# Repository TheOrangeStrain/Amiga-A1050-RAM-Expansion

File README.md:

# Amiga-A1050-RAM-Expansion
A knockoff of the A1050 front mounted RAM Expansion for the Amiga 1000

FYI: I noticed today (May 4, 2022) there is a seller on ebay [item desc: 256Kb RAM  AMIGA 1000 ( GREEN FULL SET )!!! . NEW IN STOCK] who has a number of fully assembled units for sale.  They are listed as shipping from Poland. Cost would be just over $31 USD, including shipping, to ship to the USA. 
This is NOT an endorsement of this seller.  Just passing on the information. --TOD

The problem:
I have a craiglist.com Amiga A1000 rescue. Many parts are missing. Basically I have the case, motherboard, daughterboard and power supply.  I was able to find key parts (Amiga 2000 keyboard, keyboard adapter for A1000, mouse and replacement Paula).  Howevery, the system only had 256k of RAM. This is not enough to do, well, just about anything.  Standalone RAM expansions like the A1050 are rare and often expensive if you are lucky enough to find one.  So I decided to design build my one A1050 knockoff.

Special thanks to Raffzahn on  retrocomputing.stackexchange.com. The information he supplied was critical.  Particularly since I didn't have an A1050 to probe – just online photo's and his explanation.  See this post for great info: 
https://retrocomputing.stackexchange.com/questions/5410/was-the-amiga-1000s-front-expansion-port-capable-of-anything-other-than-the-256

And the question I posted with responses from awesome and extremely helpful folks:
https://retrocomputing.stackexchange.com/questions/19893/amiga-a1050-schematic

The RAM chips are 64k x 4 bits.  Two chips are used to generate each byte.  There are low and high bytes to make up the 16 bit output.  Four pairs of chips means 64k x 4 = 256k bytes.

Drop in replacement chips (eg. From Texas Instruments) exist as well.  Other similar chips should work if the schematic is adjusted for different pinouts.  Be sure to check voltages and active levels (high / low) of course.

A fairly straight forward schematic, but I had never really thought much about RAM circuitry.  No doubt there are other ways to do this, but I wanted it to be quite similar to the original.  I used sockets for the ICs since these RAM chips have been around longer than the manufactures planned :)  Reliablity may be an issue so I wanted them to be easy to swap.  In fact, not surprisingly, 10 percent of the ones I purchased tested as bad.

There are PCB files for both unrouted and routed boards.  I find it easier to change the unrouted board then reroute nets.  I used freeRouting.jar to do the routing.

The BOM.ods file shows more detail on the parts I used.  My costs are listed and are from May and June of 2021 in U.S. Dollars.

No guarantees as I only have one A1000 to test with, but this seems to work on this system.  It would be good to hear experiences from anyone who builds one or has suggestions.

I am thinking of doing a version 2 that uses chips currently being manufactured.  If I get it working,
I will post that design and info as well.

Licencing:
CC0 1.0 Universal (CC0 1.0)
https://creativecommons.org/publicdomain/zero/1.0/

Feel free to use, modify or adapt for you own use, including commercial.

I hope this is useful for the Amiga community.
Enjoy and share.
TOD

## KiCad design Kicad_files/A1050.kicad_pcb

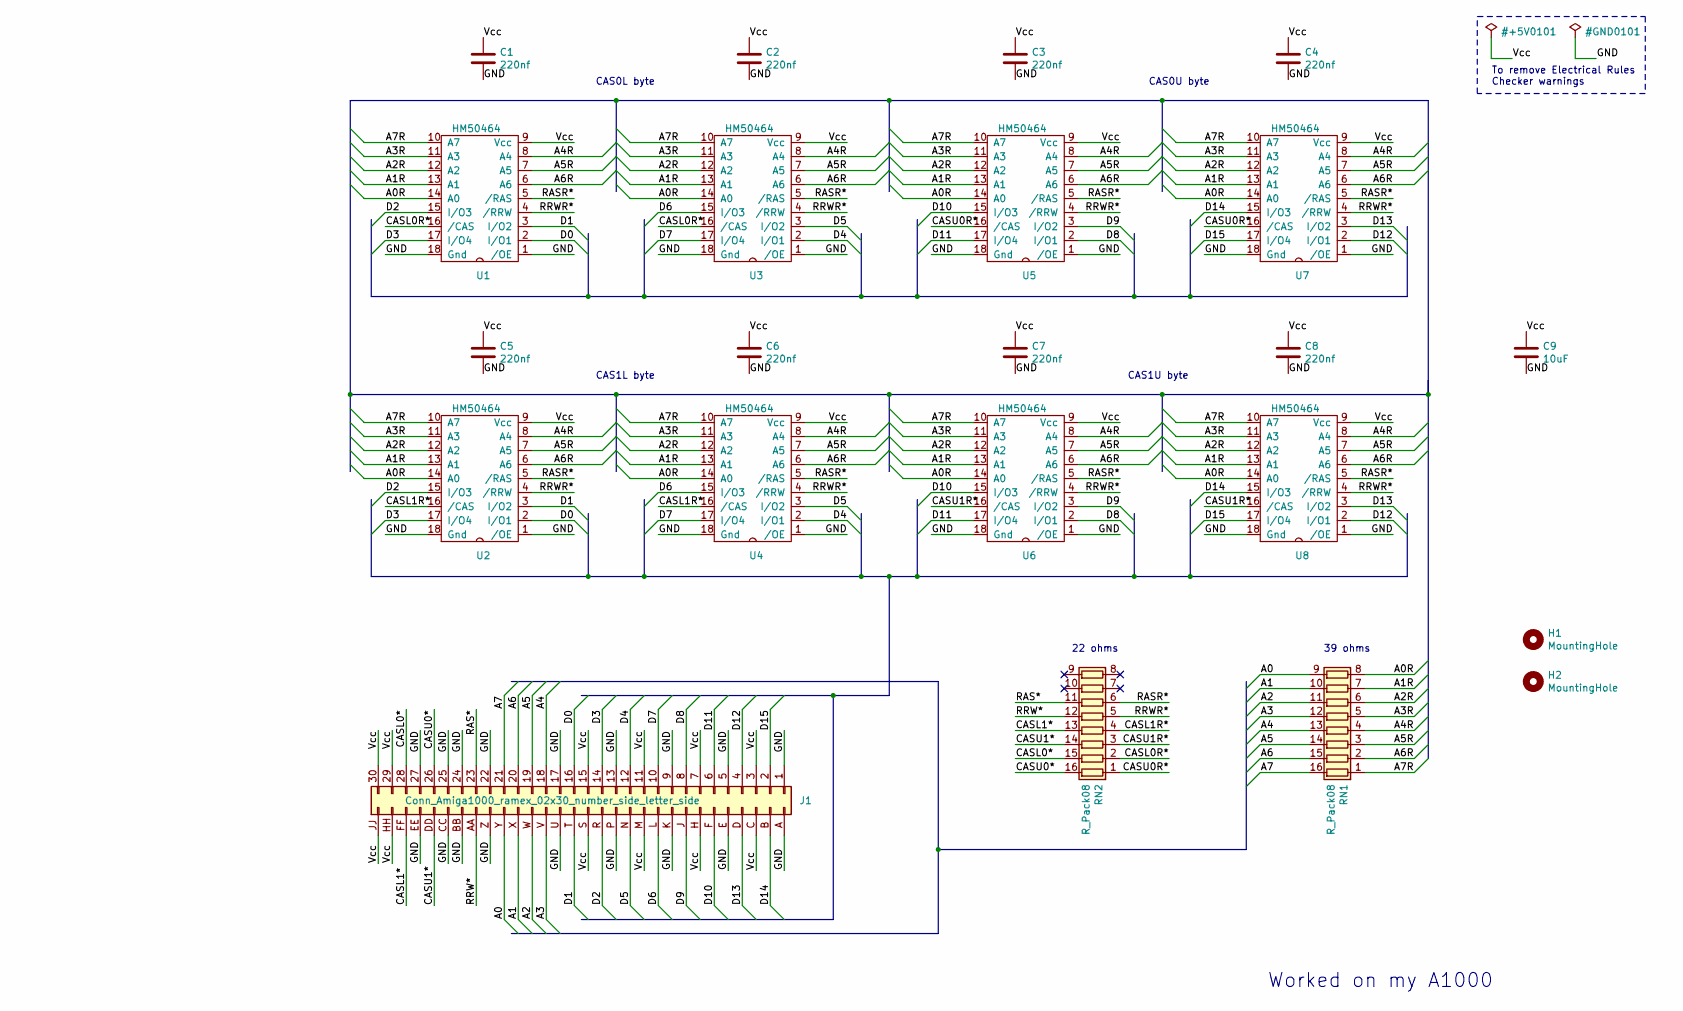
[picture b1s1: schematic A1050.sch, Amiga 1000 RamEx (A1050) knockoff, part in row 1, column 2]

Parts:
C1, C2, C3, C4, C6, C7, C8: 220nf; C_Disc_D4.3mm_W1.9mm_P5.00mm
C5: 220nf; C_Disc_D4.3mm_W1.9mm_P5.00mm; Manu Part SR215C224KARTR2
C9: 10uF; C_Disc_D4.3mm_W1.9mm_P5.00mm
H1, H2: MountingHole; MountingHole_3.5mm
J1: Conn_Amiga1000_ramex_02x30_number_side_letter_side; Connector_horizontal_amiga1.04_GREEN
RN1, RN2: R_Pack08; DIP-16_W7.62mm
U1, U2, U3, U4, U5, U6, U7, U8: HM50464; DIP-18_W7.62mm

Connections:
/A0: J1.Y, RN1.9 (R8.2)
/A0R: RN1.8 (R8.1), U1.14 (A0), U2.14 (A0), U3.14 (A0), U4.14 (A0), U5.14 (A0), U6.14 (A0), U7.14 (A0), U8.14 (A0)
/A1: J1.X, RN1.10 (R7.2)
/A1R: RN1.7 (R7.1), U1.13 (A1), U2.13 (A1), U3.13 (A1), U4.13 (A1), U5.13 (A1), U6.13 (A1), U7.13 (A1), U8.13 (A1)
/A2: J1.W, RN1.11 (R6.2)
/A2R: RN1.6 (R6.1), U1.12 (A2), U2.12 (A2), U3.12 (A2), U4.12 (A2), U5.12 (A2), U6.12 (A2), U7.12 (A2), U8.12 (A2)
/A3: J1.V, RN1.12 (R5.2)
/A3R: RN1.5 (R5.1), U1.11 (A3), U2.11 (A3), U3.11 (A3), U4.11 (A3), U5.11 (A3), U6.11 (A3), U7.11 (A3), U8.11 (A3)
/A4: J1.18, RN1.13 (R4.2)
/A4R: RN1.4 (R4.1), U1.8 (A4), U2.8 (A4), U3.8 (A4), U4.8 (A4), U5.8 (A4), U6.8 (A4), U7.8 (A4), U8.8 (A4)
/A5: J1.19, RN1.14 (R3.2)
/A5R: RN1.3 (R3.1), U1.7 (A5), U2.7 (A5), U3.7 (A5), U4.7 (A5), U5.7 (A5), U6.7 (A5), U7.7 (A5), U8.7 (A5)
/A6: J1.20, RN1.15 (R2.2)
/A6R: RN1.2 (R2.1), U1.6 (A6), U2.6 (A6), U3.6 (A6), U4.6 (A6), U5.6 (A6), U6.6 (A6), U7.6 (A6), U8.6 (A6)
/A7: J1.21, RN1.16 (R1.2)
/A7R: RN1.1 (R1.1), U1.10 (A7), U2.10 (A7), U3.10 (A7), U4.10 (A7), U5.10 (A7), U6.10 (A7), U7.10 (A7), U8.10 (A7)
/CASL0*: J1.28, RN2.15 (R2.2)
/CASL0R*: RN2.2 (R2.1), U1.16 (/CAS), U3.16 (/CAS)
/CASL1*: J1.FF, RN2.13 (R4.2)
/CASL1R*: RN2.4 (R4.1), U2.16 (/CAS), U4.16 (/CAS)
/CASU0*: J1.26, RN2.16 (R1.2)
/CASU0R*: RN2.1 (R1.1), U5.16 (/CAS), U7.16 (/CAS)
/CASU1*: J1.DD, RN2.14 (R3.2)
/CASU1R*: RN2.3 (R3.1), U6.16 (/CAS), U8.16 (/CAS)
/D0: J1.16, U1.2 (I/O1), U2.2 (I/O1)
/D1: J1.T, U1.3 (I/O2), U2.3 (I/O2)
/D2: J1.R, U1.15 (I/O3), U2.15 (I/O3)
/D3: J1.14, U1.17 (I/O4), U2.17 (I/O4)
/D4: J1.12, U3.2 (I/O1), U4.2 (I/O1)
/D5: J1.N, U3.3 (I/O2), U4.3 (I/O2)
/D6: J1.L, U3.15 (I/O3), U4.15 (I/O3)
/D7: J1.10, U3.17 (I/O4), U4.17 (I/O4)
/D8: J1.8, U5.2 (I/O1), U6.2 (I/O1)
/D9: J1.J, U5.3 (I/O2), U6.3 (I/O2)
/D10: J1.F, U5.15 (I/O3), U6.15 (I/O3)
/D11: J1.6, U5.17 (I/O4), U6.17 (I/O4)
/D12: J1.4, U7.2 (I/O1), U8.2 (I/O1)
/D13: J1.D, U7.3 (I/O2), U8.3 (I/O2)
/D14: J1.B, U7.15 (I/O3), U8.15 (I/O3)
/D15: J1.2, U7.17 (I/O4), U8.17 (I/O4)
/RAS*: J1.23, RN2.11 (R6.2)
/RASR*: RN2.6 (R6.1), U1.5 (/RAS), U2.5 (/RAS), U3.5 (/RAS), U4.5 (/RAS), U5.5 (/RAS), U6.5 (/RAS), U7.5 (/RAS), U8.5 (/RAS)
/RRW*: J1.AA, RN2.12 (R5.2)
/RRWR*: RN2.5 (R5.1), U1.4 (/RRW), U2.4 (/RRW), U3.4 (/RRW), U4.4 (/RRW), U5.4 (/RRW), U6.4 (/RRW), U7.4 (/RRW), U8.4 (/RRW)

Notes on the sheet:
CAS0L byte
Worked on my A1000
CAS1L byte
CAS0U byte
CAS1U byte
39 ohms
22 ohms
To remove Electrical Rules Checker warnings

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
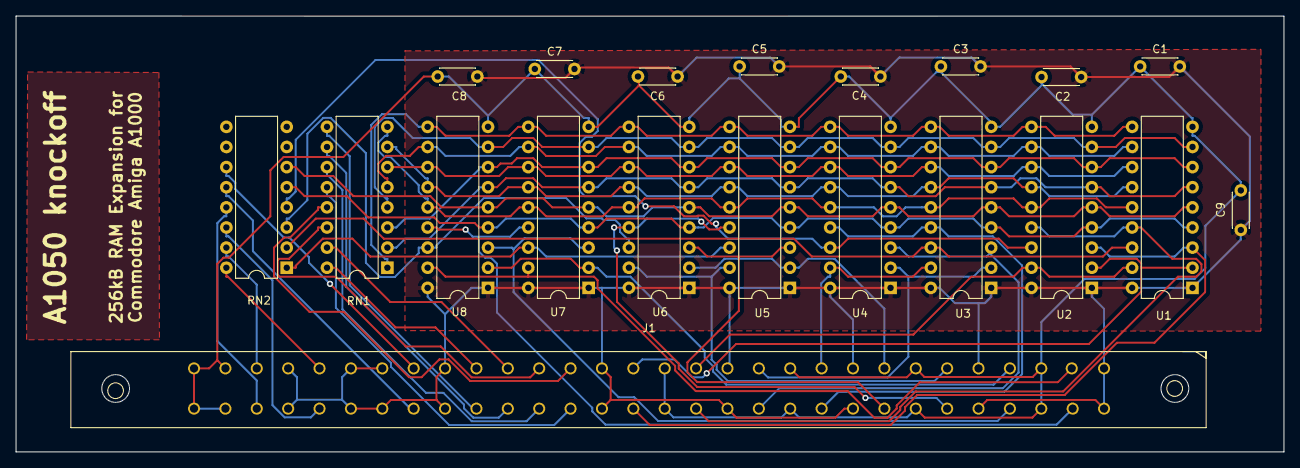
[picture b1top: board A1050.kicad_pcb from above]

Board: 2 copper layers, 160.0 x 55.0 mm, 22 parts (0 on the bottom side), 46 nets.

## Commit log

2021-07-29 Add files via upload
    Initial upload
2021-08-05 Added pics of Amiga with out and with RAM expansion
2022-02-17 Original RAMEX schematic
    I recently acquired a handful of Amiga 1000 schematics. Included was one for the RAM Expansion. It is now here for your reference.
    Enjoy,
    TheOrangeDude
2022-05-05 Update README.md
    Info on some assembled units listed on ebay.
